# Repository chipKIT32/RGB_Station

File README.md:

# RGB_Station
RGB Station project - remix of Fubarino Mini + addressable LEDs + BLE

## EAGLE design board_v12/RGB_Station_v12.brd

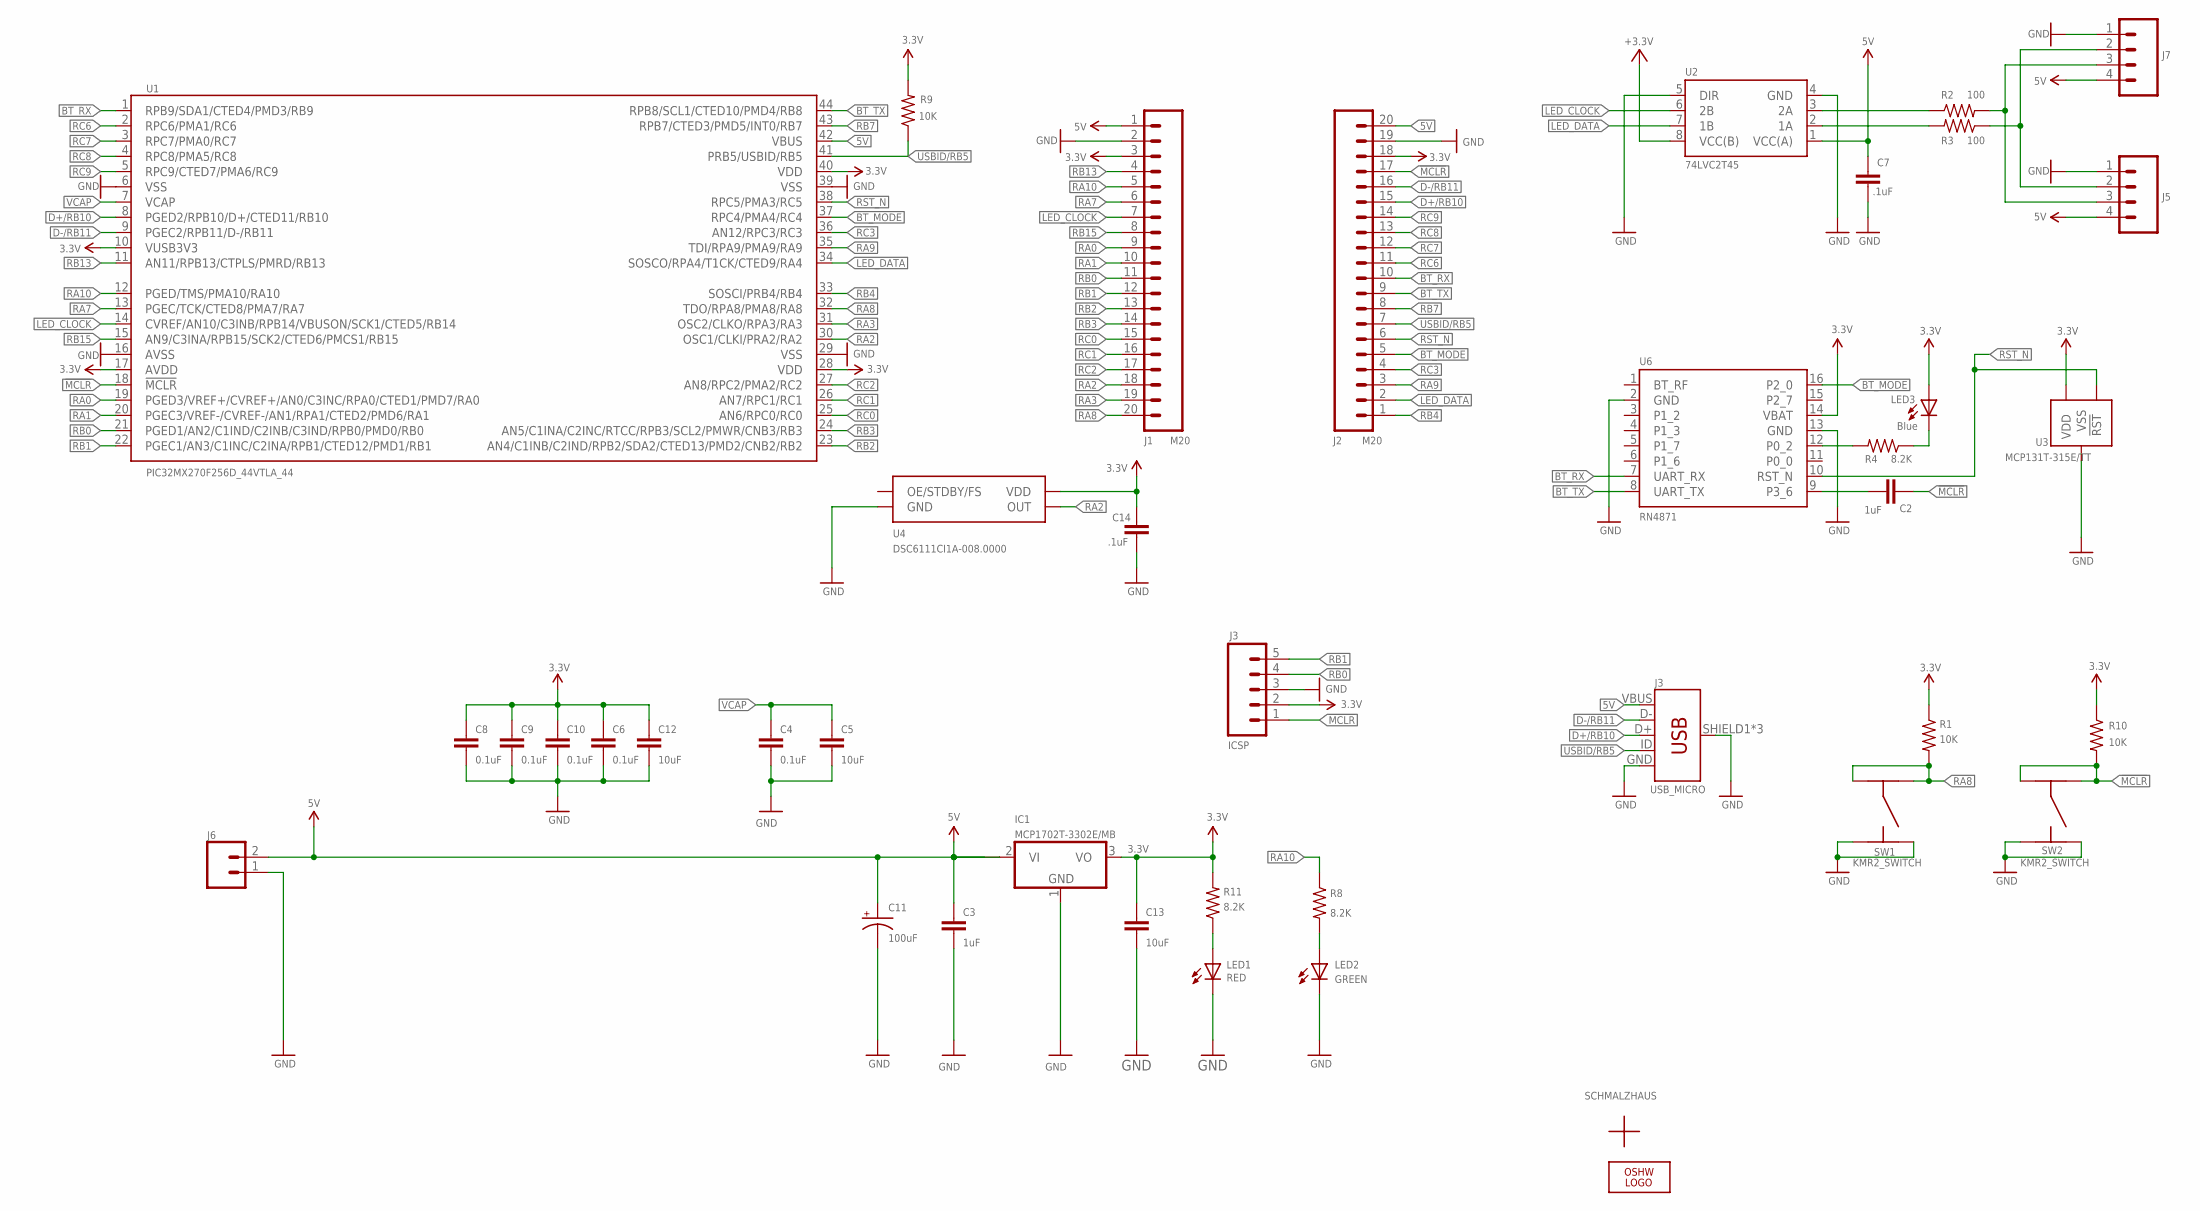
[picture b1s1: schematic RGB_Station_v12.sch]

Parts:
C2, C3: 1uF; 0603-CAP
C4, C8, C9: 0.1uF; 0603-CAP
C5, C12, C13: 10uF; 0805
C6, C10: 0.1uF; 0603
C7, C14: .1uF; 0603-CAP
C11: 100uF; PANASONIC_C
IC1: MCP1702T-3302E/MB; RGB_STATION_V12_LINEAR_SOT89
ICSP: J3; 1X05_NOSILK
J1, J2: M20; 1X20_NO_PIN1
J3: USB_MICRO; SPARKFUN-CONNECTORS_USB-B-MICRO-SMD
J5: CONN_04SCREW; SCREWTERMINAL-3.5MM-4@1
J6: CONN_023.5MM; SCREWTERMINAL-3.5MM-2
J7: M04PTH; 1X04
LED1: RED; LED-0603
LED2: GREEN; LED-0603
LED3: Blue; LED-0603
LOGO1: OSHW_LOGO_8MILX0070-NT; OSHW_8X70_NOTEXT
R1, R9, R10: 10K; 0603-RES
R2, R3: 100; 0603-RES
R4, R8, R11: 8.2K; 0603-RES
SW1, SW2: KMR2_SWITCH
U1: PIC32MX270F256D_44VTLA_44; QFN-44-8X8-NOPAD
U2: 74LVC2T45; VSSOP8
U3: MCP131T-315E/TT; SOT23-3
U4: DSC6111CI1A-008.0000; CDFN-4_3.2X2.5
U6: RN4871
U$2: CE_MARK5MM; CE_5MM
U$3: ROSH_GARBAGE; ROHS_GARBAGE_5MM
U$4: CHIPKIT2MM; CHIPKIT_2MM
U$5: SCHMALZHAUSSCHMALZHAUS_SMALL; SCHMALZHAUS_SMALL

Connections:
3.3V: C6.1, C8.1, C9.1, C10.1, C12.1, C13.1, C14.2, IC1.3 (VO), ICSP.2, J1.3, J2.18, LED3.A, R1.1, R9.2, R10.1, R11.2, U1.10 (VUSB3V3), U1.17 (AVDD), U1.28 (VDD), U1.40 (VDD), U2.8 (VCC(B)), U3.2 (VDD), U4.P4 (VDD), U6.14 (VBAT)
5V: C3.1, C7.2, C11.+, IC1.2 (VI), IC1.2@1 (VI1), J1.1, J2.20, J3.VBUS, J5.4, J6.2, J7.4, U1.42 (VBUS), U2.1 (VCC(A))
!MCLR!: C2.2, ICSP.1, J2.17, R10.2, SW2.P1, SW2.P4, U1.18 (!MCLR!)
BT_MODE: J2.5, U1.37 (RPC4/PMA4/RC4), U6.16 (P2_0)
BT_RX: J2.10, U1.1 (RPB9/SDA1/CTED4/PMD3/RB9), U6.7 (UART_RX)
BT_TX: J2.9, U1.44 (RPB8/SCL1/CTED10/PMD4/RB8), U6.8 (UART_TX)
D+/RB10: J2.15, J3.D+, U1.8 (PGED2/RPB10/D+/CTED11/RB10)
D-/RB11: J2.16, J3.D-, U1.9 (PGEC2/RPB11/D-/RB11)
GND: C3.2, C4.2, C5.2, C6.2, C7.1, C8.2, C9.2, C10.2, C11.-, C12.2, C13.2, C14.1, IC1.1 (GND), ICSP.3, J1.2, J2.19, J3.GND, J3.SHIELD1 (SHIELD), J3.SHIELD2 (SHIELD), J3.SHIELD3 (SHIELD), J5.1, J6.1, J7.1, LED1.C, LED2.C, SW1.P2, SW1.P3, SW2.P2, SW2.P3, U1.6 (VSS), U1.16 (AVSS), U1.29 (VSS), U1.39 (VSS), U2.4 (GND), U2.5 (DIR), U3.3 (VSS), U4.P2 (GND), U6.2 (GND), U6.13 (GND)
LED_CLOCK: J1.7, U1.14 (CVREF/AN10/C3INB/RPB14/VBUSON/SCK1/CTED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), U2.6 (2B)
LED_DATA: J2.2, U1.34 (SOSCO/RPA4/T1CK/CTED9/RA4), U2.7 (1B)
unnamed: R4.2, U6.12 (P0_2)
unnamed: J5.2, J7.2, R3.1
unnamed: R3.2, U2.2 (1A)
unnamed: J5.3, J7.3, R2.2
unnamed: LED3.C, R4.1
unnamed: LED1.A, R11.1
unnamed: C2.1, U6.9 (P3_6)
unnamed: LED2.A, R8.2
unnamed: R2.1, U2.3 (2A)
RA0: J1.9, U1.19 (PGED3/VREF+/CVREF+/AN0/C3INC/RPA0/CTED1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)
RA1: J1.10, U1.20 (PGEC3/VREF-/CVREF-/AN1/RPA1/CTED2/PMD6/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)
RA2: J1.18, U1.30 (OSC1/CLKI/PRA2/RA2), U4.P3 (OUT)
RA3: J1.19, U1.31 (OSC2/CLKO/RPA3/RA3)
RA7: J1.6, U1.13 (PGEC/TCK/CTED8/PMA7/RA7)
RA8: J1.20, R1.2, SW1.P1, SW1.P4, U1.32 (TDO/RPA8/PMA8/RA8)
RA9: J2.3, U1.35 (TDI/RPA9/PMA9/RA9)
RA10: J1.5, R8.1, U1.12 (PGED/TMS/PMA10/RA10)
RB0: ICSP.4, J1.11, U1.21 (PGED1/AN2/C1IND/C2INB/C3IND/RPB0/PMD0/R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)
RB1: ICSP.5, J1.12, U1.22 (PGEC1/AN3/C1INC/C2INA/RPB1/CTED12/PMD1/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)
RB2: J1.13, U1.23 (AN4/C1INB/C2IND/RPB2/SDA2/CTED13/PMD2/C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)
RB3: J1.14, U1.24 (AN5/C1INA/C2INC/RTCC/RPB3/SCL2/PMWR/CNB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)
RB4: J2.1, U1.33 (SOSCI/PRB4/RB4)
RB7: J2.8, U1.43 (RPB7/CTED3/PMD5/INT0/RB7)
RB13: J1.4, U1.11 (AN11/RPB13/CTPLS/PMRD/RB13)
RB15: J1.8, U1.15 (AN9/C3INA/RPB15/SCK2/CTED6/PMCS1/RB15)
RC0: J1.15, U1.25 (AN6/RPC0/RC0)
RC1: J1.16, U1.26 (AN7/RPC1/RC1)
RC2: J1.17, U1.27 (AN8/RPC2/PMA2/RC2)
RC3: J2.4, U1.36 (AN12/RPC3/RC3)
RC6: J2.11, U1.2 (RPC6/PMA1/RC6)
RC7: J2.12, U1.3 (RPC7/PMA0/RC7)
RC8: J2.13, U1.4 (RPC8/PMA5/RC8)
RC9: J2.14, U1.5 (RPC9/CTED7/PMA6/RC9)
RST_N: J2.6, U1.38 (RPC5/PMA3/RC5), U3.1 (!RST!), U6.10 (RST_N)
USBID/RB5: J2.7, J3.ID, R9.1, U1.41 (PRB5/USBID/RB5)
VCAP: C4.1, C5.1, U1.7 (VCAP)

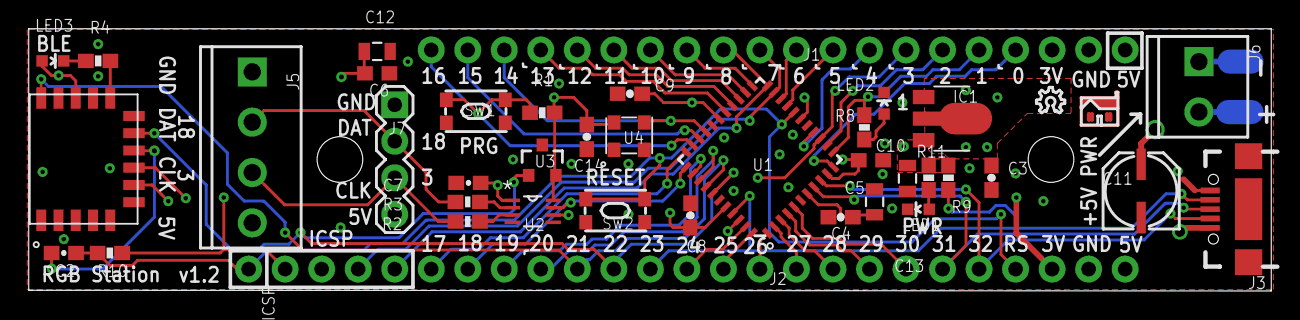
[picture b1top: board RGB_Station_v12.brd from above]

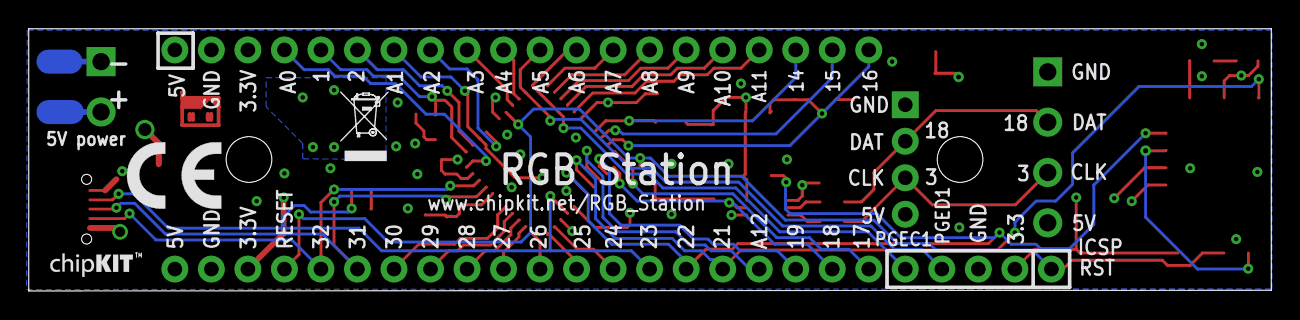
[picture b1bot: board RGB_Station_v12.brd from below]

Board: 4 copper layers, 86.4 x 18.2 mm, 44 parts (3 on the bottom side), 47 nets.

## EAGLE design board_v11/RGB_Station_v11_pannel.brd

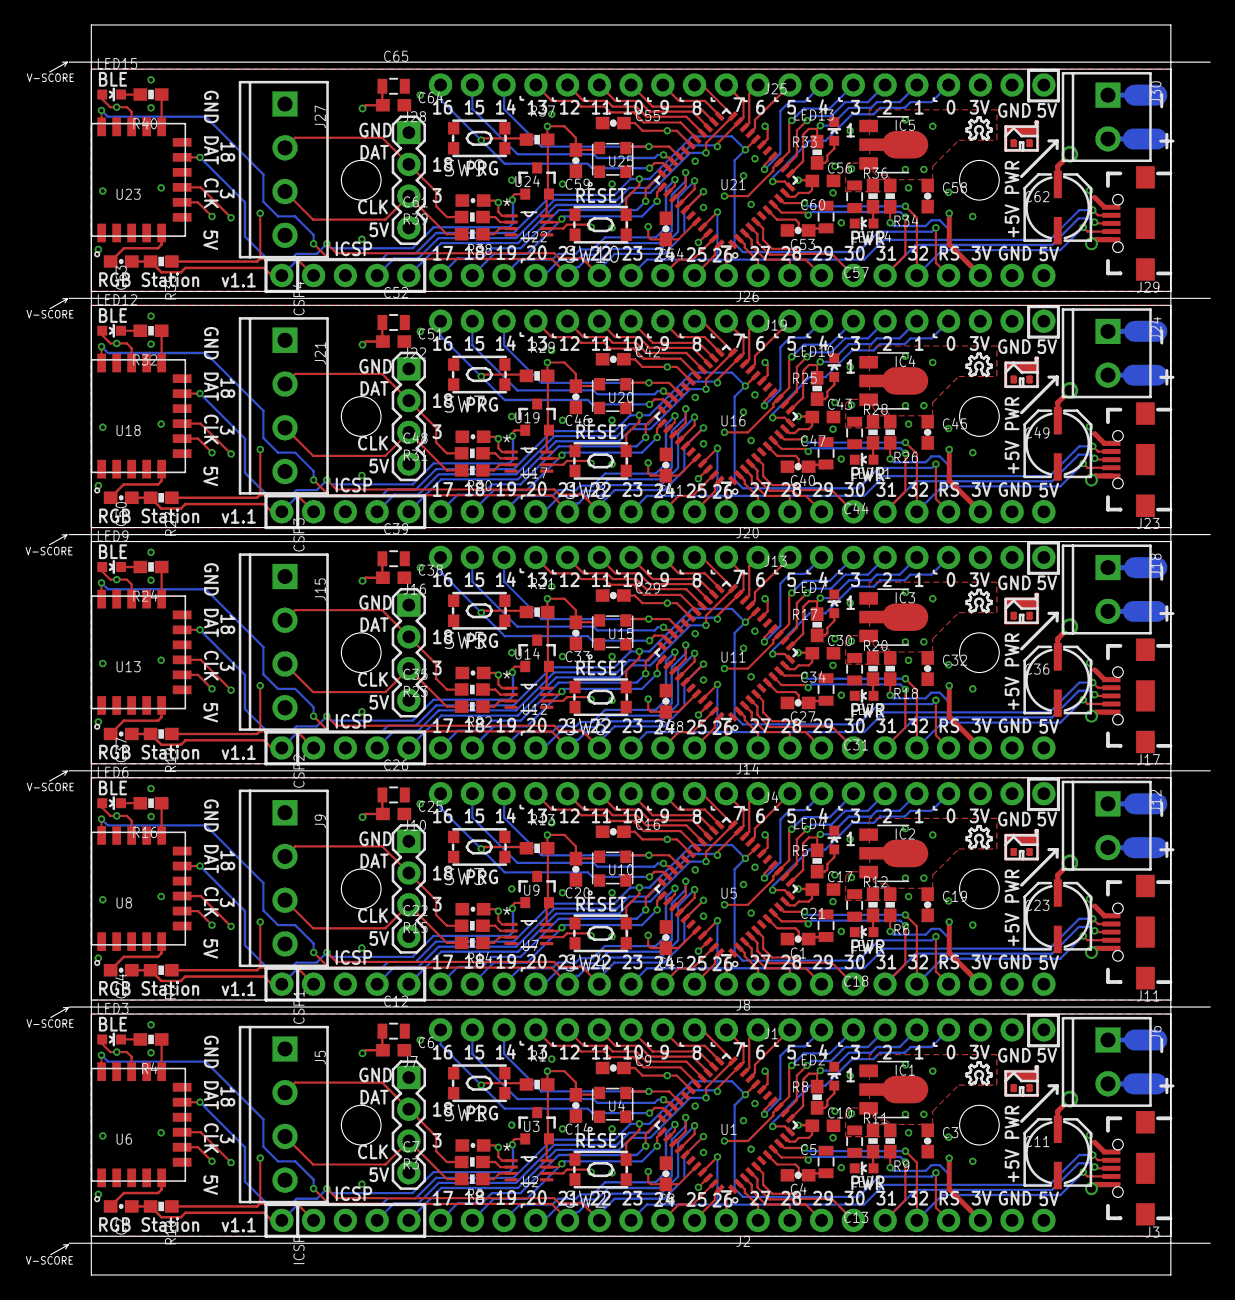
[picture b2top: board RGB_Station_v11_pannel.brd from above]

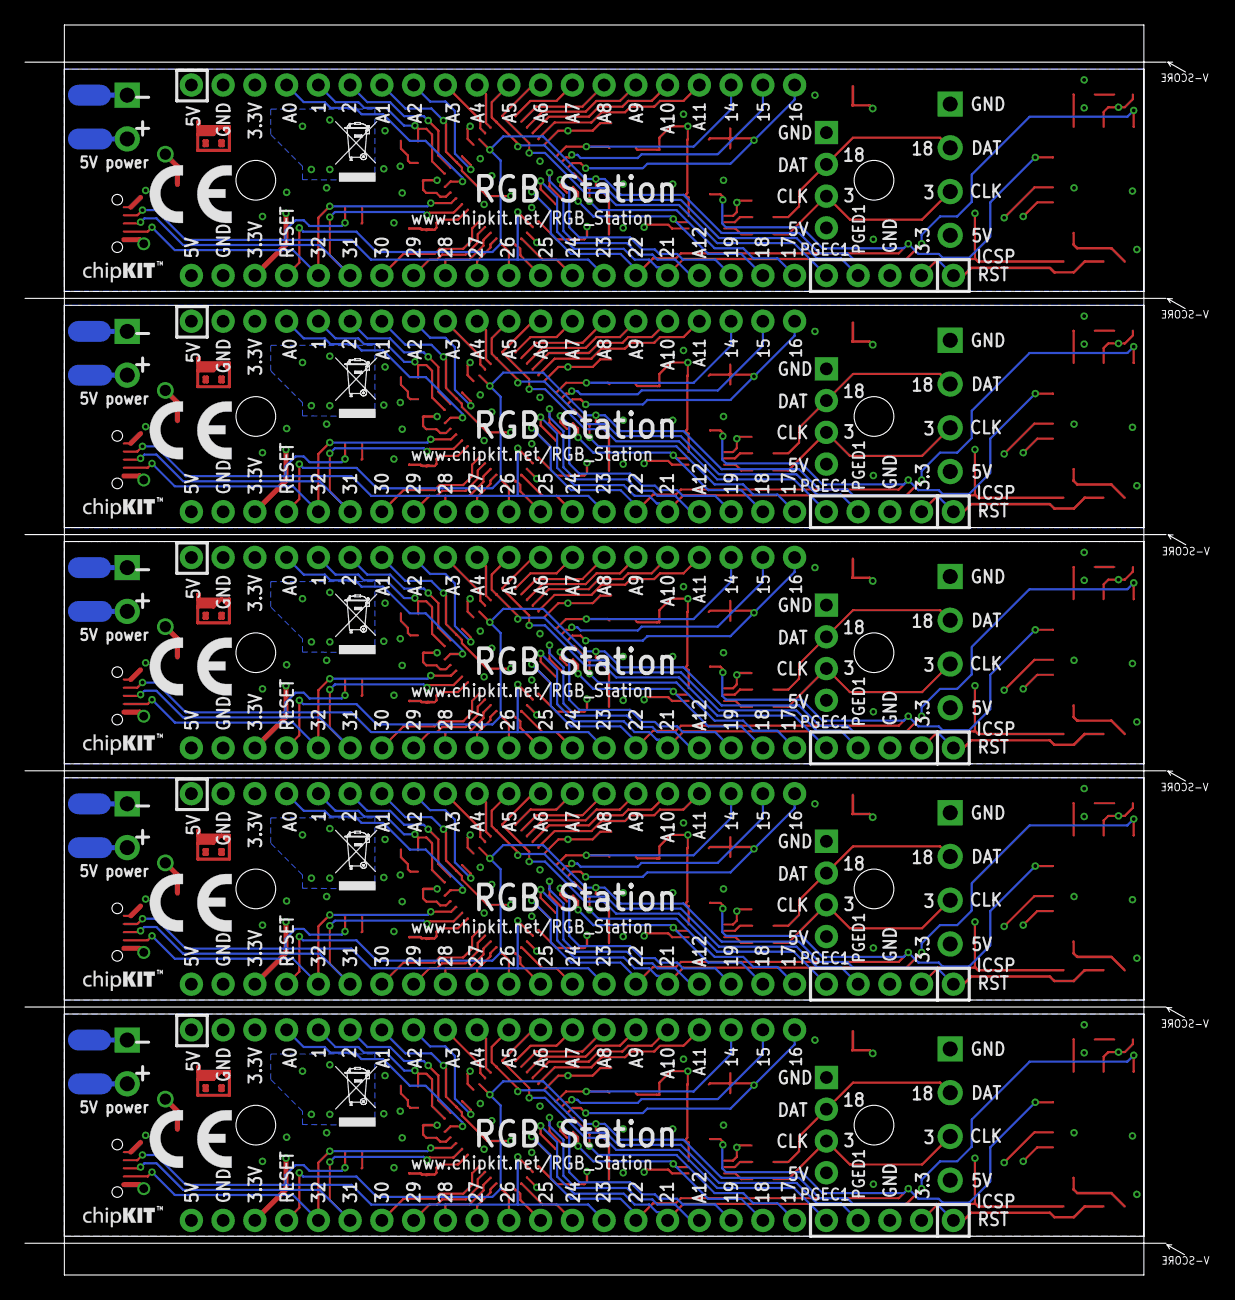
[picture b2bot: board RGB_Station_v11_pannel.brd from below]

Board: 4 copper layers, 94.8 x 100.0 mm, 220 parts (15 on the bottom side), 235 nets.

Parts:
C1, C4, C8, C9, C15, C16, C27, C28, C29, C40, C41, C42, C53, C54, C55: 0.1uF; 0603-CAP
C2, C7, C14, C20, C22, C24, C33, C35, C37, C46, C48, C50, C59, C61, C63: .1uF; 0603-CAP
C3, C19, C32, C45, C58: 1uF; 0603-CAP
C5, C12, C13, C18, C21, C26, C31, C34, C39, C44, C47, C52, C57, C60, C65: 10uF; 0805
C6, C10, C17, C25, C30, C38, C43, C51, C56, C64: 0.1uF; 0603
C11, C23, C36, C49, C62: 100uF; PANASONIC_C
IC1, IC2, IC3, IC4, IC5: MCP1702T-3302E/MB; SOT89
ICSP, ICSP1, ICSP2, ICSP3, ICSP4: J3; 1X05_NOSILK
J1, J2, J4, J8, J13, J14, J19, J20, J25, J26: M20; 1X20_NO_PIN1
J3, J11, J17, J23, J29: USB_MICRO; USB-B-MICRO-SMD
J5, J9, J15, J21, J27: SCREWTERMINAL-3.5MM-4@1
J6, J12, J18, J24, J30: SCREWTERMINAL-3.5MM-2
J7, J10, J16, J22, J28: 1X04
LED1, LED5, LED8, LED11, LED14: RED; LED-0603
LED2, LED4, LED7, LED10, LED13: GREEN; LED-0603
LED3, LED6, LED9, LED12, LED15: Blue; LED-0603
LOGO1, LOGO2, LOGO3, LOGO4, LOGO5: OSHW_LOGO_8MILX0070-NT; OSHW_8X70_NOTEXT
R1, R6, R7, R9, R10, R13, R18, R19, R21, R26, R27, R29, R34, R35, R37: 10K; 0603-RES
R2, R3, R14, R15, R22, R23, R30, R31, R38, R39: 100; 0603-RES
R4, R5, R8, R11, R12, R16, R17, R20, R24, R25, R28, R32, R33, R36, R40: 8.2K; 0603-RES
SW1, SW2, SW3, SW4, SW5, SW6, SW7, SW8, SW9, SW10: KMR2_SWITCH
U1, U5, U11, U16, U21: PIC32MX270F256D_44VTLA_44; QFN-44-8X8-NOPAD
U2, U7, U12, U17, U22: 74LVC2T45; VSSOP8
U3, U9, U14, U19, U24: MCP121T-315E/TT; SOT23-3
U4, U10, U15, U20, U25: DSC6111CI1A-008.0000; CDFN-4_3.2X2.5
U6, U8, U13, U18, U23: RN4871
U$1, U$2, U$9, U$13, U$17: CE_MARK5MM; CE_5MM
U$3, U$6, U$10, U$14, U$18: ROSH_GARBAGE; ROHS_GARBAGE_5MM
U$4, U$7, U$11, U$15, U$19: CHIPKIT2MM; CHIPKIT_2MM
U$5, U$8, U$12, U$16, U$20: SCHMALZHAUSSCHMALZHAUS_SMALL; SCHMALZHAUS_SMALL

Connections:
3.3V: C6.1, C8.1, C9.1, C10.1, C12.1, C13.1, C14.2, IC1.3, ICSP.2, J1.3, J2.18, LED3.A, R1.1, R9.2, R10.1, R11.2, U1.10, U1.17, U1.28, U1.40, U2.8, U3.2, U4.P4, U6.14
3.3V1: C15.1, C16.1, C17.1, C18.1, C20.2, C25.1, C26.1, IC2.3, ICSP1.2, J4.3, J8.18, LED6.A, R6.2, R7.1, R12.2, R13.1, U5.10, U5.17, U5.28, U5.40, U7.8, U8.14, U9.2, U10.P4
3.3V2: C28.1, C29.1, C30.1, C31.1, C33.2, C38.1, C39.1, IC3.3, ICSP2.2, J13.3, J14.18, LED9.A, R18.2, R19.1, R20.2, R21.1, U11.10, U11.17, U11.28, U11.40, U12.8, U13.14, U14.2, U15.P4
3.3V3: C41.1, C42.1, C43.1, C44.1, C46.2, C51.1, C52.1, IC4.3, ICSP3.2, J19.3, J20.18, LED12.A, R26.2, R27.1, R28.2, R29.1, U16.10, U16.17, U16.28, U16.40, U17.8, U18.14, U19.2, U20.P4
3.3V4: C54.1, C55.1, C56.1, C57.1, C59.2, C64.1, C65.1, IC5.3, ICSP4.2, J25.3, J26.18, LED15.A, R34.2, R35.1, R36.2, R37.1, U21.10, U21.17, U21.28, U21.40, U22.8, U23.14, U24.2, U25.P4
5V: C3.1, C7.2, C11.+, IC1.2, IC1.2@1, J1.1, J2.20, J3.VBUS, J5.4, J6.2, J7.4, U1.42, U2.1
5V1: C19.1, C22.2, C23.+, IC2.2, IC2.2@1, J4.1, J8.20, J9.4, J10.4, J11.VBUS, J12.2, U5.42, U7.1
5V2: C32.1, C35.2, C36.+, IC3.2, IC3.2@1, J13.1, J14.20, J15.4, J16.4, J17.VBUS, J18.2, U11.42, U12.1
5V3: C45.1, C48.2, C49.+, IC4.2, IC4.2@1, J19.1, J20.20, J21.4, J22.4, J23.VBUS, J24.2, U16.42, U17.1
5V4: C58.1, C61.2, C62.+, IC5.2, IC5.2@1, J25.1, J26.20, J27.4, J28.4, J29.VBUS, J30.2, U21.42, U22.1
!MCLR!: C2.2, ICSP.1, J2.17, R10.2, SW2.P3, SW2.P4, U1.18
!MCLR!1: C24.2, ICSP1.1, J8.17, R7.2, SW4.P3, SW4.P4, U5.18
!MCLR!2: C37.2, ICSP2.1, J14.17, R19.2, SW6.P3, SW6.P4, U11.18
!MCLR!3: C50.2, ICSP3.1, J20.17, R27.2, SW8.P3, SW8.P4, U16.18
!MCLR!4: C63.2, ICSP4.1, J26.17, R35.2, SW10.P3, SW10.P4, U21.18
BT_MODE: J2.5, U1.37, U6.16
BT_MODE1: J8.5, U5.37, U8.16
BT_MODE2: J14.5, U11.37, U13.16
BT_MODE3: J20.5, U16.37, U18.16
BT_MODE4: J26.5, U21.37, U23.16
BT_RX: J2.10, U1.1, U6.7
BT_RX1: J8.10, U5.1, U8.7
BT_RX2: J14.10, U11.1, U13.7
BT_RX3: J20.10, U16.1, U18.7
BT_RX4: J26.10, U21.1, U23.7
BT_TX: J2.9, U1.44, U6.8
BT_TX1: J8.9, U5.44, U8.8
BT_TX2: J14.9, U11.44, U13.8
BT_TX3: J20.9, U16.44, U18.8
BT_TX4: J26.9, U21.44, U23.8
D+/RB1: J8.15, J11.D+, U5.8
D+/RB2: J14.15, J17.D+, U11.8
D+/RB3: J20.15, J23.D+, U16.8
D+/RB4: J26.15, J29.D+, U21.8
D+/RB10: J2.15, J3.D+, U1.8
D-/RB1: J8.16, J11.D-, U5.9
D-/RB2: J14.16, J17.D-, U11.9
D-/RB3: J20.16, J23.D-, U16.9
D-/RB4: J26.16, J29.D-, U21.9
D-/RB11: J2.16, J3.D-, U1.9
GND: C3.2, C4.2, C5.2, C6.2, C7.1, C8.2, C9.2, C10.2, C11.-, C12.2, C13.2, C14.1, IC1.1, ICSP.3, J1.2, J2.19, J3.GND, J3.SHIELD1, J3.SHIELD2, J3.SHIELD3, J5.1, J6.1, J7.1, LED1.C, LED2.C, SW1.P1, SW1.P2, SW2.P1, SW2.P2, U1.6, U1.16, U1.29, U1.39, U2.4, U2.5, U3.3, U4.P2, U6.2, U6.13
GND1: C1.2, C15.2, C16.2, C17.2, C18.2, C19.2, C20.1, C21.2, C22.1, C23.-, C25.2, C26.2, IC2.1, ICSP1.3, J4.2, J8.19, J9.1, J10.1, J11.GND, J11.SHIELD1, J11.SHIELD2, J11.SHIELD3, J12.1, LED4.C, LED5.C, SW3.P1, SW3.P2, SW4.P1, SW4.P2, U5.6, U5.16, U5.29, U5.39, U7.4, U7.5, U8.2, U8.13, U9.3, U10.P2
GND2: C27.2, C28.2, C29.2, C30.2, C31.2, C32.2, C33.1, C34.2, C35.1, C36.-, C38.2, C39.2, IC3.1, ICSP2.3, J13.2, J14.19, J15.1, J16.1, J17.GND, J17.SHIELD1, J17.SHIELD2, J17.SHIELD3, J18.1, LED7.C, LED8.C, SW5.P1, SW5.P2, SW6.P1, SW6.P2, U11.6, U11.16, U11.29, U11.39, U12.4, U12.5, U13.2, U13.13, U14.3, U15.P2
GND3: C40.2, C41.2, C42.2, C43.2, C44.2, C45.2, C46.1, C47.2, C48.1, C49.-, C51.2, C52.2, IC4.1, ICSP3.3, J19.2, J20.19, J21.1, J22.1, J23.GND, J23.SHIELD1, J23.SHIELD2, J23.SHIELD3, J24.1, LED10.C, LED11.C, SW7.P1, SW7.P2, SW8.P1, SW8.P2, U16.6, U16.16, U16.29, U16.39, U17.4, U17.5, U18.2, U18.13, U19.3, U20.P2
GND4: C53.2, C54.2, C55.2, C56.2, C57.2, C58.2, C59.1, C60.2, C61.1, C62.-, C64.2, C65.2, IC5.1, ICSP4.3, J25.2, J26.19, J27.1, J28.1, J29.GND, J29.SHIELD1, J29.SHIELD2, J29.SHIELD3, J30.1, LED13.C, LED14.C, SW9.P1, SW9.P2, SW10.P1, SW10.P2, U21.6, U21.16, U21.29, U21.39, U22.4, U22.5, U23.2, U23.13, U24.3, U25.P2
LED_CLOCK: J1.7, U1.14, U2.6
LED_CLOCK1: J4.7, U5.14, U7.6
LED_CLOCK2: J13.7, U11.14, U12.6
LED_CLOCK3: J19.7, U16.14, U17.6
LED_CLOCK4: J25.7, U21.14, U22.6
LED_DATA: J2.2, U1.34, U2.7
LED_DATA1: J8.2, U5.34, U7.7
LED_DATA2: J14.2, U11.34, U12.7
LED_DATA3: J20.2, U16.34, U17.7
LED_DATA4: J26.2, U21.34, U22.7
unnamed: R4.2, U6.12
unnamed: J5.2, J7.2, R3.1
unnamed: R3.2, U2.2
unnamed: J5.3, J7.3, R2.2
unnamed: LED3.C, R4.1
unnamed: LED1.A, R11.1
unnamed: LED5.A, R12.1
unnamed: C2.1, U6.5
unnamed: J9.3, J10.3, R14.2
unnamed: R14.1, U7.3
unnamed: LED2.A, R8.2
unnamed: J9.2, J10.2, R15.1
unnamed: R15.2, U7.2
unnamed: C24.1, U8.5
unnamed: LED4.A, R5.2
unnamed: R16.2, U8.12
unnamed: LED6.C, R16.1
unnamed: LED8.A, R20.1
unnamed: J15.3, J16.3, R22.2
unnamed: R22.1, U12.3
unnamed: J15.2, J16.2, R23.1
unnamed: R23.2, U12.2
unnamed: R2.1, U2.3
unnamed: C37.1, U13.5
unnamed: LED7.A, R17.2
unnamed: R24.2, U13.12
unnamed: LED9.C, R24.1
unnamed: LED11.A, R28.1
unnamed: J21.3, J22.3, R30.2
unnamed: R30.1, U17.3
unnamed: J21.2, J22.2, R31.1
unnamed: R31.2, U17.2
unnamed: C50.1, U18.5
unnamed: LED10.A, R25.2
unnamed: R32.2, U18.12
unnamed: LED12.C, R32.1
unnamed: LED14.A, R36.1
unnamed: J27.3, J28.3, R38.2
unnamed: R38.1, U22.3
unnamed: J27.2, J28.2, R39.1
unnamed: R39.2, U22.2
unnamed: C63.1, U23.5
unnamed: LED13.A, R33.2
unnamed: R40.2, U23.12
unnamed: LED15.C, R40.1
RA0: J1.9, U1.19
RA1: J1.10, U1.20
RA2: J1.18, U1.30, U4.P3
RA3: J1.19, U1.31
RA4: J4.19, U5.31
RA5: J4.18, U5.30, U10.P3
RA6: J8.3, U5.35
RA7: J1.6, U1.13
RA8: J1.20, R1.2, SW1.P3, SW1.P4, U1.32
RA9: J2.3, U1.35
RA10: J1.5, R8.1, U1.12
RA11: J4.20, R13.2, SW3.P3, SW3.P4, U5.32
RA12: J4.5, R5.1, U5.12
RA13: J4.6, U5.13
RA14: J4.9, U5.19
RA15: J4.10, U5.20
RA16: J13.19, U11.31
RA17: J13.18, U11.30, U15.P3
RA18: J14.3, U11.35
RA19: J13.20, R21.2, SW5.P3, SW5.P4, U11.32
RA20: J13.5, R17.1, U11.12
RA21: J13.6, U11.13
RA22: J13.9, U11.19
RA23: J13.10, U11.20
RA24: J19.19, U16.31
RA25: J19.18, U16.30, U20.P3
RA26: J20.3, U16.35
RA27: J19.20, R29.2, SW7.P3, SW7.P4, U16.32
RA28: J19.5, R25.1, U16.12
RA29: J19.6, U16.13
RA30: J19.9, U16.19
RA31: J19.10, U16.20
RA32: J25.19, U21.31
RA33: J25.18, U21.30, U25.P3
RA34: J26.3, U21.35
RA35: J25.20, R37.2, SW9.P3, SW9.P4, U21.32
RA36: J25.5, R33.1, U21.12
RA37: J25.6, U21.13
RA38: J25.9, U21.19
RA39: J25.10, U21.20
RB0: ICSP.4, J1.11, U1.21
RB1: ICSP.5, J1.12, U1.22
RB2: J1.13, U1.23
RB3: J1.14, U1.24
RB4: J2.1, U1.33
RB5: J4.4, U5.11
RB6: J4.8, U5.15
RB7: J2.8, U1.43
RB8: ICSP1.5, J4.12, U5.22
RB9: ICSP1.4, J4.11, U5.21
RB10: J8.8, U5.43
RB11: J4.14, U5.24
RB12: J4.13, U5.23
RB13: J1.4, U1.11
RB14: J8.1, U5.33
RB15: J1.8, U1.15
RB16: J13.4, U11.11
RB17: J13.8, U11.15
RB18: ICSP2.5, J13.12, U11.22
RB19: ICSP2.4, J13.11, U11.21
RB20: J14.8, U11.43
RB21: J13.14, U11.24
RB22: J13.13, U11.23
RB23: J14.1, U11.33
RB24: J19.4, U16.11
RB25: J19.8, U16.15
RB26: ICSP3.5, J19.12, U16.22
RB27: ICSP3.4, J19.11, U16.21
RB28: J20.8, U16.43
RB29: J19.14, U16.24
RB30: J19.13, U16.23
RB31: J20.1, U16.33
RB32: J25.4, U21.11
RB33: J25.8, U21.15
RB34: ICSP4.5, J25.12, U21.22
RB35: ICSP4.4, J25.11, U21.21
RB36: J26.8, U21.43
RB37: J25.14, U21.24
RB38: J25.13, U21.23
RB39: J26.1, U21.33
RC0: J1.15, U1.25
RC1: J1.16, U1.26
RC2: J1.17, U1.27
RC3: J2.4, U1.36
RC4: J8.4, U5.36
RC5: J4.17, U5.27
RC6: J2.11, U1.2
RC7: J2.12, U1.3
RC8: J2.13, U1.4
RC9: J2.14, U1.5
RC10: J4.16, U5.26
RC11: J4.15, U5.25
RC12: J8.11, U5.2
RC13: J8.12, U5.3
RC14: J8.13, U5.4
RC15: J8.14, U5.5
RC16: J14.4, U11.36
RC17: J13.17, U11.27
RC18: J13.16, U11.26
RC19: J13.15, U11.25
RC20: J14.11, U11.2
RC21: J14.12, U11.3
RC22: J14.13, U11.4
RC23: J14.14, U11.5
RC24: J20.4, U16.36
RC25: J19.17, U16.27
RC26: J19.16, U16.26
RC27: J19.15, U16.25
RC28: J20.11, U16.2
RC29: J20.12, U16.3
RC30: J20.13, U16.4
RC31: J20.14, U16.5
RC32: J26.4, U21.36
RC33: J25.17, U21.27
RC34: J25.16, U21.26
RC35: J25.15, U21.25
RC36: J26.11, U21.2
RC37: J26.12, U21.3
RC38: J26.13, U21.4
RC39: J26.14, U21.5
RST_N: J2.6, U1.38, U3.1, U6.10
RST_N1: J8.6, U5.38, U8.10, U9.1
RST_N2: J14.6, U11.38, U13.10, U14.1
RST_N3: J20.6, U16.38, U18.10, U19.1
RST_N4: J26.6, U21.38, U23.10, U24.1
USBID/RB1: J8.7, J11.ID, R6.1, U5.41
USBID/RB2: J14.7, J17.ID, R18.1, U11.41
USBID/RB3: J20.7, J23.ID, R26.1, U16.41
USBID/RB4: J26.7, J29.ID, R34.1, U21.41
USBID/RB5: J2.7, J3.ID, R9.1, U1.41
VCAP: C4.1, C5.1, U1.7
VCAP1: C1.1, C21.1, U5.7
VCAP2: C27.1, C34.1, U11.7
VCAP3: C40.1, C47.1, U16.7
VCAP4: C53.1, C60.1, U21.7

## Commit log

2017-11-17 Initial check in : v1.0 of board has been sent off for fab, not built or tested yet.
2017-11-25 Starting v1.1 of the board - changes listed in notes.txt
2017-11-26 Updated switches with proper footprint.
2017-11-26 Routed new switches, tweaked layout a bit - blue LED now on very end.
2017-11-29 Added pin numbers to CLK and DAT output silk screen
2017-11-30 Version 1.1 complete and ready for fab.
2017-12-03 Version 1.1 sent out for board fab.
2017-12-14 Created v1.2 : fixed schematic problem with switches being always grounded.
2017-12-16 Generated gerbers for v1.2
2018-01-09 PDFs of schematics added for v1.1 and v1.2 boards.
2018-02-16 Updates to v1.2 : Made two screw terminals DNPs, and changed C2 from .1uf to 1uF to help with preventing resetting of PIC32 when RN does firmware update.
2018-02-18 Updated v1.2 board for PCB:NG production - changed DRC rules to minimize violations. Updated .1uF cap and red LED with alternate parts. Updated USB footprint to be exactly correct for Wurth USB conne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
2018-02-19 Updated U2 (level shifter) to alternate part that's available (same package, no board change).
2018-02-19 Updated note on schematic about using open-drain reset controller, not push-pull.
2018-02-27 Added centroid file
2018-02-28 Updated refdes for switches to SW1 and SW2.
2018-03-07 Working on updating centroid/BOM to work with PCB:NG without errors/changes. Not there yet (four parts to fix)
2018-03-08 Finished centroid file for PCB:NG automation. Updated some library footprints.
2018-03-14 Fixed PCB:NG CAM inner layer problem, regenerated gerbers. Far fewer DFM errors now. Still have minimum mask to mask distance errors though.
2018-03-15 Got all PCB:NG DFM errors to go away - * Added large stop mask rectangles custom versions of USB, level shifter and PIC32 parts to fix stop mask too close errors * Fixed CAM file to include pads laye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
2018-04-17 Starting work on RGB Station pin diagram
2018-04-18 More work on Pin diagram
2018-04-20 More work on pin diagram.
2018-04-21 Pin diagram - almost done.
2018-04-22 Done with pin diagram.
2018-04-24 Updated pin diagram to mention not to use 3.3V pin as power input if using LEDs.

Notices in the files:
board_v12/RGB_Station_v12.sch:
Copyright 2017 Guy McCarthy. Copyright and related rights are licensed under the Solderpad Hardware License, Version 0.51 (the “License”);
software, hardware and materials distributed under this License is distributed on an “AS IS” BASIS, WITHOUT WARRANTIES OR CONDITIONS OF ANY KIND, either express or implied.
parts and their libraries:
SparkFun-Connectors: Licensing: Creative Commons ShareAlike 4.0 International - https://creativecommons.org/licenses/by-sa/4.0
